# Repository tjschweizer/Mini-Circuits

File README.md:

# Mini-Circuits

A repository for my files from my Mini Circuit series at learn-cnc.com

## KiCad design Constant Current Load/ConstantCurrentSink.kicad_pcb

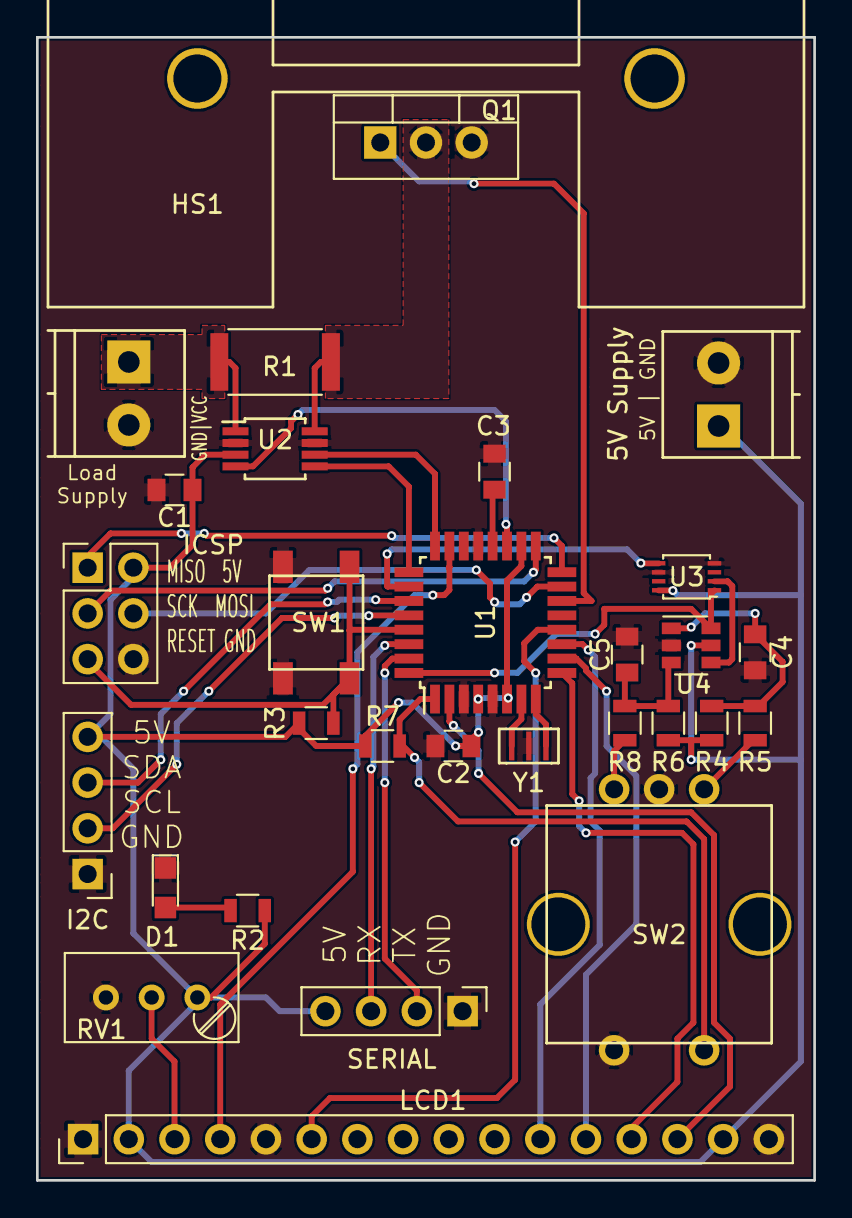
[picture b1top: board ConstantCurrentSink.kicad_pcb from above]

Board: 2 copper layers, 43.2 x 63.5 mm, 30 parts (0 on the bottom side), 35 nets.

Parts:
C1, C2, C4, C5: 1uF; C_0805
C3: 100nF; C_0805
D1: LED; LED_0805
HS1: HS380-ND; Aavid5290
J1: Load Supply; TerminalBlock_Phoenix_PT-3.5mm_2pol
J2: 5V Supply; TerminalBlock_Phoenix_PT-3.5mm_2pol
J3: ICSP; Pin_Header_Straight_2x03_Pitch2.54mm
J4: I2C; Pin_Header_Straight_1x04_Pitch2.54mm
J5: SERIAL; Pin_Header_Straight_1x04_Pitch2.54mm
LCD1: LCD-00255; Pin_Header_Straight_1x16_Pitch2.54mm
Q1: Q_NMOS_GDS; TO-220-3_Vertical
R1: 5mΩ; R_2512
R2, R3: 1K; R_0805
R4, R6: 3k; R_0805
R5, R8: 220; R_0805
R7: 10K; R_0805
RV1: POT; Potentiometer_Trimmer_Bourns_3296W
SW1: SW_Push; KPT-1187B
SW2: Rotary_Encoder_Switch; TW-700198
U1: ATMEGA328P-AU; TQFP-32_7x7mm_Pitch0.8mm
U2: INA225; MSOP-8_3x3mm_Pitch0.65mm
U3: SN74LVC2G14; SOT-23-6
U4: SN74LVC2G74; VSSOP-8_2.4x2.1mm_Pitch0.5mm
Y1: 16MHz; CSTCE_V

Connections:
+5V: C1.1, C2.1, J2.1, J3.2, J4.4, J5.4, LCD1.2, LCD1.15, R2.1, R3.1, R4.2, R6.2, R7.1, RV1.1, U1.4, U1.6, U1.18, U2.3, U3.5, U4.8
/A0: LCD1.4, U1.23
/A1: U1.24, U2.6
/A2: U1.25, U2.5
/A3/DIR: U1.26, U4.5
/A4: J4.3, U1.27
/A5: J4.2, U1.28
/A6: U1.19, U2.4
/D0/RX: J5.3, U1.30
/D1/TX: J5.2, U1.31
/D2/STEP: U1.32, U3.6, U4.1
/D3: R7.2, SW2.4, U1.1
/D4: LCD1.14, U1.2
/D5: LCD1.13, U1.9
/D6: LCD1.12, U1.10
/D7: LCD1.11, U1.11
/D8: LCD1.6, U1.12
/D10: Q1.1, U1.14
/D11/MOSI: J3.4, U1.15
/D12/MISO: J3.1, U1.16
/D13/SCK: J3.3, U1.17
/ENC_A: R5.2, SW2.1
/ENC_B: R8.2, SW2.3
/RESET: J3.5, R3.2, SW1.1, U1.29
GND: C1.2, C2.2, C3.2, C4.2, C5.2, D1.1, J1.2, J2.2, J3.6, J4.1, J5.1, LCD1.1, LCD1.5, LCD1.16, Q1.3, RV1.3, SW1.2, SW2.2, SW2.5, U1.3, U1.5, U1.21, U2.2, U2.7, U3.2, U4.4, U4.6, Y1.2
unnamed: C3.1, U1.20
unnamed: C4.1, R4.1, R5.1, U3.1
unnamed: C5.1, R6.1, R8.1, U3.3
unnamed: D1.2, R2.2
unnamed: LCD1.3, RV1.2
unnamed: Q1.2, R1.1, U2.8
unnamed: U1.7, Y1.3
unnamed: U1.8, Y1.1
unnamed: U3.4, U4.2
VCC: J1.1, R1.2, U2.1

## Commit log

2018-04-15 Create tmp
2018-05-07 Updated Schematic
    More details at learn-cnc.com/mini-circuit-1-constant-current-sink-update-2
